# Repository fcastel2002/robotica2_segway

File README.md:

# Segway con patas extensibles

Trabajo final de **Robótica II**, Universidad Nacional de Cuyo (UNCUYO). Grupo 4: Joaquín Calderón
(modelado), Francisco Castel (diseño mecánico), Matías Armani (simulación en Simulink y electrónica), Ignacio Bartolini y Mariano Gimenez.

**Este archivo describe el robot tal como es hoy.** Todo lo que había de propuestas anteriores
(mecanismo de Hoeken, motores N20, plantas de simulación de agosto y principios de septiembre) se
borró del árbol el 19/9/2026 y quedó solo en la historia de git; ver la sección 7.

## Componentes comprados — actualización del 15/10/2026

El [inventario confirmado](electronica/componentes_comprados/inventario/inventario_robotica.md)
y los [datasheets y fichas recopilados](electronica/componentes_comprados/datasheets/README.md)
están organizados en [electrónica](electronica/componentes_comprados/README.md).
Se registran **14 entradas y 27 dispositivos/conjuntos** (un pack contiene tres celdas), incluidos **2 servos DSSERVO DS3240 MG** y
**2 motores GA25-370 de 12 V y 300 RPM con encoder**. ESP32 y MPU6050 confirmadas;
alimentación representada por una fuente nominal de 11,1 V. Matías es responsable de electrónica y PCB.
[Plan de trabajo](electronica/planificacion/2026-10-15-plan-electronica-pcb.md).

El modelo y la simulación **ya usan el motor comprado** desde el 15/10 (PAR-004 y ELE-014 en el
[backlog](BACKLOG.md)). Lo que sigue pendiente es el CAD, que todavía tiene el motor anterior de 37 mm
y al que le falta la rueda (CAD-202 y PAR-003). Cuidado con la ficha del vendedor: su columna de
torsión se contradice con la eléctrica, así que el par del modelo está **calculado**, no leído.

## 1. Qué es el robot

Un robot de dos ruedas que se equilibra como un péndulo invertido (tipo Segway) y que además tiene
**patas extensibles**: cada rueda cuelga de un mecanismo de cuatro barras movido por un servo, así
que el robot puede agacharse, pararse y bajar escalones absorbiendo el golpe con las patas.

- **Equilibrio y avance**: los dos motores de rueda, con encoder, controlados por un LQR sobre la
  inclinación y la velocidad (a diseñar sobre el modelo de la planta completa).
- **Patas**: un servo por pata. El servo es de posición; se le manda una trayectoria de ángulo y su
  lazo interno hace el par. La dinámica de la pata sirve para dimensionarlo, no para comandarlo.
- **Cabina**: caja impresa en PLA que lleva los dos servos, la batería y la electrónica. Los pivotes
  del cuatro barras (A, el eje del servo, y B) están en sus paredes laterales.

## 2. Números vigentes (19/9/2026)

Fuente única de todos los valores: [`modelado/parametros/parametros_fisicos.m`](modelado/parametros/parametros_fisicos.m),
variante `segunda_iteracion`. Si un número de este README no coincide con ese archivo, manda el archivo.

| | Valor | De dónde sale |
|---|---|---|
| Mecanismo | cuatro barras `A B C D` con acoplador rígido `C D P`; `P` es el eje de la rueda | `modelado/geometria/geometria_robot.png` |
| Barras | AD = 112, BC = 108, CD = 40,8, DP = 112 mm (familia 1,40 / 1,35 / 0,51 / 1,40 a escala 80); δ = 164° | medido en los STEP de `diseño_mecanico/segunda_iteracion/completo/step/` |
| Bancada AB | 80 mm a 45° (intención). En el STEP está en 77,9 mm a 46,6°: B quedó 3 mm corto en horizontal, a corregir en `cabeza_v31` | idem |
| Recorrido del servo | 320° (pata estirada, de pie) a 350° (plegada). En la dinámica se usa θ = 360° − servo: 10° plegada, 40° estirada | `parametros_geometria.m` |
| Rueda | Ø80 mm (Rw = 40), **50 g medidos** (22/10/2026) | Matías (radio), pesada |
| Servo de pata | **40 kg·cm**, ~58 g, uno por pata. Elegido el 19/9; verificar a qué tensión da los 40 kg·cm | decisión, ver sección 3 |
| Motor de rueda | **GA25-370 12 V, reductor 1:20, 300 rpm en vacío**, con encoder de cuadratura (11 PPR en el rotor). **96 g medidos** (22/10/2026). **Comprado** | decisión, ver sección 3 |
| Masas **medidas** (21 y 22/10/2026) | barras por pata: AD 30 g, BC 23 g, CDP 11 g (pesadas una por una); caja 542 g (se pesó el robot sin ruedas ni motores de rueda: 670 g, y se restaron las seis barras); rueda 50 g y motor de rueda 96 g; **robot 962 g** | el BC resultó **4 veces** más pesado que el estimado, la caja 19 % más liviana y la rueda 67 % más pesada. **Ya no queda ninguna masa estimada** |
| Batería | LiPo 3S 11,1 V (propuesta) | |
| Control | 200 Hz (propuesta); electrónica por definir | |

Lo que sale de esos números (par estático del servo, inercia vista por el servo, altura de la cabina,
qué escalón se puede bajar, fuerzas en los pasadores) está en los PDF de `modelado/`, sección 4.

## 3. Decisiones tomadas y por qué

| Fecha | Decisión | Motivo | Dónde está |
|---|---|---|---|
| ago 2026 | Mecanismo de Hoeken con flexor → **cuatro barras** con acoplador rígido | el cuatro barras da una línea casi recta para el eje de rueda con un solo servo, y es más fácil de imprimir | `modelado/geometria/` |
| 2/9 | Barras en la familia 1,40 / 1,35 / 0,51 / 1,40 con δ = 164° | salió de un barrido de proporciones (scripts de Francisco, ya borrados; ver sección 7) | `parametros_fisicos.m` |
| 3/9 | Motor JGA25 de 60 rpm **descartado** | la simulación mostró que con 60 rpm el robot equilibra pero no puede desplazarse ni bajar escalones; hace falta encoder sí o sí | `base_conocimiento/dimensiones_cad_primera_iteracion.md` |
| 14/9 | CAD segunda iteración: barras a **escala 80** | la primera iteración tenía la bancada de 80 mm con barras de escala 100 y perdía la línea recta; Francisco llevó las barras a 80 | `diseño_mecanico/segunda_iteracion/` |
| 19/9 | El modelado pasa a escala 80 para seguir al CAD | eran dos ramas de la misma bifurcación; imprimir es lo caro, así que manda el CAD | `docs/gestion/2026-09-19-auditoria-limpieza.md`, sección 1.2 |
| 19/9 | Servo de **40 kg·cm** | con la geometría de escala 100 la caída de un escalón de 18 cm pedía 22,4 kg·cm de par medio; uno de 25 quedaba justo y uno de 35 no se consigue | `modelado/dinamica/dinamica_resumen.pdf`, sección 10 |
| 15/10 | Motor de rueda **GA25-370 1:20** (comprado) | 300 rpm en vacío dan 1,01 m/s con la rueda de 66 mm. El par y el agarre quedan casi empatados: el motor pone 6,0 N en el piso contra 6,9 N de fricción disponible. La columna de torsión de su ficha es inconsistente y no se usa | `modelado/parametros/parametros_fisicos.m` §7 |
| 19/9 | `simulacion/planta_v2` (planta completa hecha con Claude) se descarta | el equipo va a rehacer la planta a mano en `modelado/planta/`; queda el banco Simulink de Matías | sección 7 |

## 4. Mapa del repositorio

Nuevo el 1/10/2026: [**modelo dinámico del péndulo invertido, desarrollado paso a paso**](modelado/planta/pendulo_invertido/desarrollo_matematico.md).
Representa el equilibrio y avance con las patas fijas en una postura configurable. La demostración
en MATLAB está en [`simulacion/pendulo_invertido/`](simulacion/pendulo_invertido/README.md); abrir
`SIMULAR_PENDULO_INVERTIDO.m` y pulsar Run. La planta conjunta con flexión dinámica sigue pendiente.

| Carpeta | Qué hay | Responsable |
|---|---|---|
| [`modelado/`](modelado/) | **El modelo del robot.** Una carpeta por tema: `geometria/` (figura con nombres y cotas), `cinematica/` (θ → posiciones, directa e inversa), `dcl/` (diagramas de cuerpo libre), `dinamica/` (Lagrange de la pata, tres casos, caída de escalón, fuerza en el eje del servo), `parametros/` (la fuente única de valores). Cada tema tiene su PDF con la deducción. Ver [`modelado/README.md`](modelado/README.md) | Joaquín (modelado), Matías (API y `parametros/`) |
| [`diseño_mecanico/`](diseño_mecanico/) | `3er_iteracion/`: el CAD vigente de la pata (SolidWorks + STEP). `chasis nuevo/`: ensamble del chasis con la cabina, el servo y el lugar de la PCB. `utilidades/`: piezas compradas (servo, horn, motores, sensor, rueda, tornillería). Las iteraciones anteriores se borraron el 1/11 y siguen en git. Ver [`diseño_mecanico/README.md`](diseño_mecanico/README.md) | Francisco |
| [`simulacion/`](simulacion/) | `dinamica_pata_v1/`: primera iteración del banco Simulink de la pata (Matías, 14 y 15/9), punto de entrada `INICIAR_DINAMICA_PATA.m`. Ver [`simulacion/README.md`](simulacion/README.md) | Matías |
| [`ensayos/`](ensayos/README.md) | Experimentos con el robot real, repetibles: un protocolo `.json` por experimento, `correr.py` lo ejecuta por WiFi y deja una carpeta por corrida, `revisar.py` controla lo grabado. Nació con la cosimulación robot ↔ Simulink (9/11) | Francisco |
| [`gui_hmi/`](gui_hmi/) | Interfaz web para ver las variables del robot en tiempo real (WiFi o USB) y grabarlas a CSV. `python gui_hmi/puente.py --simular` y abrir http://localhost:8000. Ver [`gui_hmi/README.md`](gui_hmi/README.md) | |
| [`docs/gestion/`](docs/gestion/) | Plan, guía de QA y traspaso del banco Simulink; auditoría de limpieza del 19/9 | Matías, Joaquín |
| [`base_conocimiento/`](base_conocimiento/) | `dimensiones_cad_primera_iteracion.md`: cotas, masas, centros de masa e inercias medidos sobre el STEP de la primera iteración (2/9). Sigue vigente para masas; para cotas manda la segunda iteración | |
| [`guias_catedra/`](guias_catedra/) | Procedimientos de la cátedra (dimensionamiento de batería, preselección de servos) | |
| [`BACKLOG.md`](BACKLOG.md) | Lo hecho, lo en curso y lo pendiente, con evidencia. Es la lista de tareas del equipo | todos |
| [`AGENTS.md`](AGENTS.md) | Reglas para agentes y colaboradores (PDF → Markdown antes de leer, backlog, diagramas) | |
| [`electronica/`](electronica/README.md) | Inventario de compras, capturas, datasheets, fichas y fuentes; integración eléctrica pendiente | Matías |
| `firmware/`, `referencias/` | Firmware pendiente; referencias de apoyo | |

## 5. Qué falta (lo grande)

Detalle y estado en [`BACKLOG.md`](BACKLOG.md).

1. ~~**Pesar** las piezas impresas, el servo y el motor~~: hecho el 21 y el 22/10/2026 (robot de 962 g). Falta la inercia de la rueda (disco o aro), ver M-4 del [plan de ensayos](docs/gestion/2026-10-21-plan-de-ensayos.md).
2. **Medir el motor**: par de bloqueo real con un brazo y una balanza, y rendimiento del reductor. La ficha del GA25-370 se contradice a sí misma (su columna de torsión exigiría 146 % de rendimiento), así que el par del modelo está calculado, no leído.
3. **Medir el servo** en el banco: rigidez del lazo interno (grados de desvío por peso colgado) y par de
   calado real a la tensión que se use. De eso dependen todos los números de la caída de escalón.
4. Corregir en el CAD los 3 mm de la bancada (`cabeza_v31`) y agregar rueda, motor y tapa al ensamble
   de la segunda iteración, para poder cerrar la ficha de masas (CAD-201).
5. **Planta completa** en `modelado/planta/`: péndulo invertido sobre ruedas con la altura del centro de
   masa en función de θ, LQR, motores, contacto. Es el modelo del equilibrio; el banco de Matías es el
   de la pata.
6. Electrónica: [plan, requisitos y ensayos definidos](electronica/README.md); validar el prototipo y después diseñar la PCB. Firmware de prueba e integración pendientes.

## 6. Cómo correr las cosas

- Figuras: `python modelado/<tema>/<figura>.py` genera el PNG al lado (Python 3 + matplotlib).
- Dinámica de la pata: abrir `modelado/dinamica/dinamica_pata.m` en MATLAB y correrlo. La sección 1
  tiene los parámetros para editar; las demás imprimen tablas y grafican.
- Tests: desde la raíz, `runtests('modelado/dinamica/tests')` y
  `runtests('simulacion/dinamica_pata_v1/tests')`.
- Banco Simulink: `simulacion/dinamica_pata_v1/INICIAR_DINAMICA_PATA.m` (ver su README).
- PDF: cada `*.tex` se compila con `pdflatex` dos veces desde su carpeta.
- Medir el CAD sin SolidWorks: los scripts de `diseño_mecanico/medir_step/` se borraron el 1/11; se recuperan con
  `git checkout 2867761 -- "diseño_mecanico/medir_step"`.

## 7. Historia: lo que hubo antes y dónde encontrarlo

Hasta el 19/9 el repo arrastraba tres diseños anteriores y sus simulaciones, y cualquiera que entrara
(persona o IA) no sabía cuál era el vigente. Se borró todo lo anterior al cuatro barras y las plantas
de simulación descartadas. La lista completa, con el motivo de cada borrado, está en
[`docs/gestion/2026-09-19-auditoria-limpieza.md`](docs/gestion/2026-09-19-auditoria-limpieza.md).
Todo sigue en git: `git show eca3ed4:<ruta>` recupera cualquier archivo tal como estaba antes de la limpieza.

| Qué era | Dónde estaba | Por qué ya no |
|---|---|---|
| Mecanismo de Hoeken, robot de 800 g con rueda Ø80 y flexor (documento de dimensionamiento de agosto) | `base_conocimiento/Segway-Pata-Dimensionamiento.docx`, `simulacion/hoekens_dh.html` | reemplazado por el cuatro barras |
| Concepto con motores N20 y microservos SG90 | `diseño_mecanico/proof_of_concept/` | reemplazado |
| Primer boceto del cuatro barras y síntesis en MotionGen | `diseño_mecanico/4_bar_mechanism/`, `4 barras.motiongen` | reemplazado por `primera_iteracion` |
| GUI y barrido de proporciones de las barras (Francisco, 28/8) | `simulacion/simular_pata_segway.m`, `optimizar_barrido_local.m` | cumplieron su función; las proporciones quedaron en `parametros_fisicos.m` |
| CAD primera iteración (bancada 80 a 47,5°, barras 100) | `diseño_mecanico/primera_iteracion/*.SLDPRT` | reemplazado por la segunda; queda el STEP y las masas |
| CAD primera y segunda iteración, soporte de mesa, STEP para imprimir y scripts `medir_step` (borrados el 1/11/2026) | `diseño_mecanico/primera_iteracion/`, `segunda_iteracion/`, `soporte_mesa/`, `step_printing/`, `medir_step/`, `outputs/` | Francisco dejó solo `3er_iteracion/`, `chasis nuevo/` y `utilidades/`; se recuperan con `git checkout 2867761 -- "diseño_mecanico/<carpeta>"` |
| Plantas Simulink `modelo_base`, `planta_v1` (borradas el 13/9) y `planta_v2` (19/9), con su manual y sus specs | `simulacion/`, `docs/informe_planta_v1/`, `docs/superpowers/` | el equipo rehace la planta a mano; queda el banco de Matías |
| Toolbox de Peter Corke copiado entero (120 MB) | `modelado/cinematica/rtb`, `smtb`, `common` | librería de terceros; `verificar_cinematica_4barras.m` sigue andando sin ella |

## 8. Convenciones

- Origen en A (eje del servo), y hacia arriba. En las figuras de la pata el frente del robot queda a la
  izquierda. Los segmentos se nombran por sus extremos: AB, AD, BC, CD, DP.
- Los PDF no se leen directamente: se convierten a Markdown primero (regla de [`AGENTS.md`](AGENTS.md)).
- Un valor físico vive en un solo lugar, `parametros_fisicos.m`. Las figuras de Python repiten las
  cinco cotas al principio de cada script porque no leen MATLAB; si cambian las barras, cambiarlas ahí también.

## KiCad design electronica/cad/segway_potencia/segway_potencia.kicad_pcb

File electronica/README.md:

# Electrónica

**Para continuar en una sesión nueva de Claude Code: [INICIAR_AQUI.md](INICIAR_AQUI.md).** Abrir Claude Code desde la raíz del repositorio. Camino confirmado: **KiCad + IA + MCP**, en **Windows**; Matías instalará KiCad. Estado al día en [estado actual](agente/memoria/estado_actual.md).

- [Plan de electrónica y PCB](planificacion/2026-10-15-plan-electronica-pcb.md).
- Borradores del 17/10: [contrato de interfaces](interfaces/2026-10-17-contrato-interfaces-borrador.md), [distribución de energía](interfaces/2026-10-17-distribucion-energia-borrador.md), [datos físicos faltantes](componentes_comprados/2026-10-17-datos-fisicos-faltantes.md).
- Entorno: [informe Windows](agente/2026-10-17-informe-entorno-windows.md) y [evaluación de MCP para KiCad](agente/2026-10-17-evaluacion-mcp-kicad.md).
- [Research de Reddit sobre EDA con IA y MCP](planificacion/2026-10-15-research-reddit-eda-ia.md).
- [Requisitos y decisiones](requisitos_y_decisiones.md).
- [Ensayos de banco](ensayos/plan_de_ensayos.md).
- [Componentes comprados y documentación](componentes_comprados/README.md).
- [Inventario detallado](componentes_comprados/inventario/inventario_robotica.md).
- [Datasheets, fichas y fuentes](componentes_comprados/datasheets/README.md).

Actualizado el 15 de octubre de 2026. Las compras confirmadas incluyen dos DS3240 MG y dos GA25-370 de 12 V y 300 RPM con encoder. La validación eléctrica de los módulos genéricos y la integración con CAD/modelado siguen pendientes en [BACKLOG.md](../BACKLOG.md).

Controladora e IMU confirmadas: **ESP32 y MPU6050**. Alimentación representada como **fuente nominal de 11,1 V** por pedido de Matías. Responsable de electrónica y PCB: **Matías**.

**Criterio confirmado para las PCB (15/10/2026):** usar los componentes como módulos completos con pines o sus conexiones físicas reales. La placa interconecta estos módulos. Aplicar [REQ-22 y sus criterios de símbolos, huellas y montaje](requisitos_y_decisiones.md) en todo diseño.

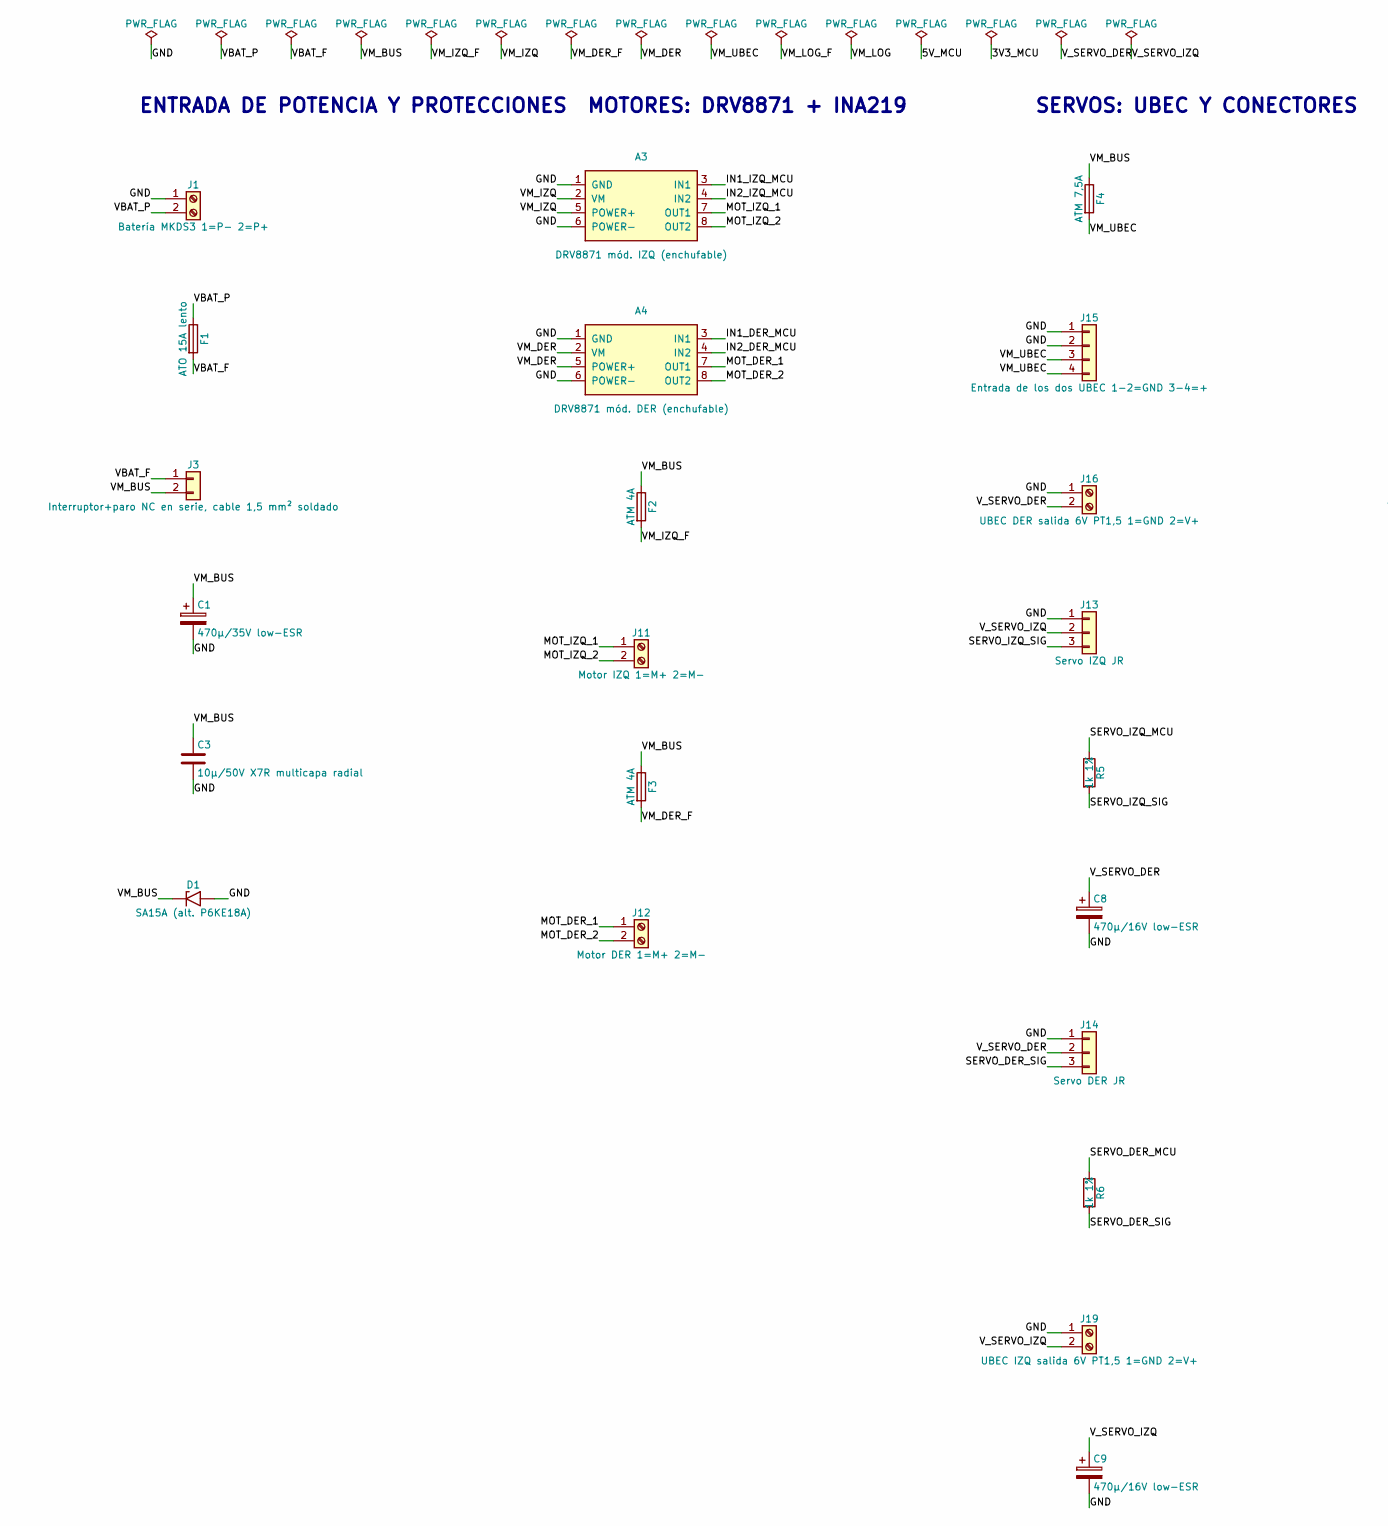
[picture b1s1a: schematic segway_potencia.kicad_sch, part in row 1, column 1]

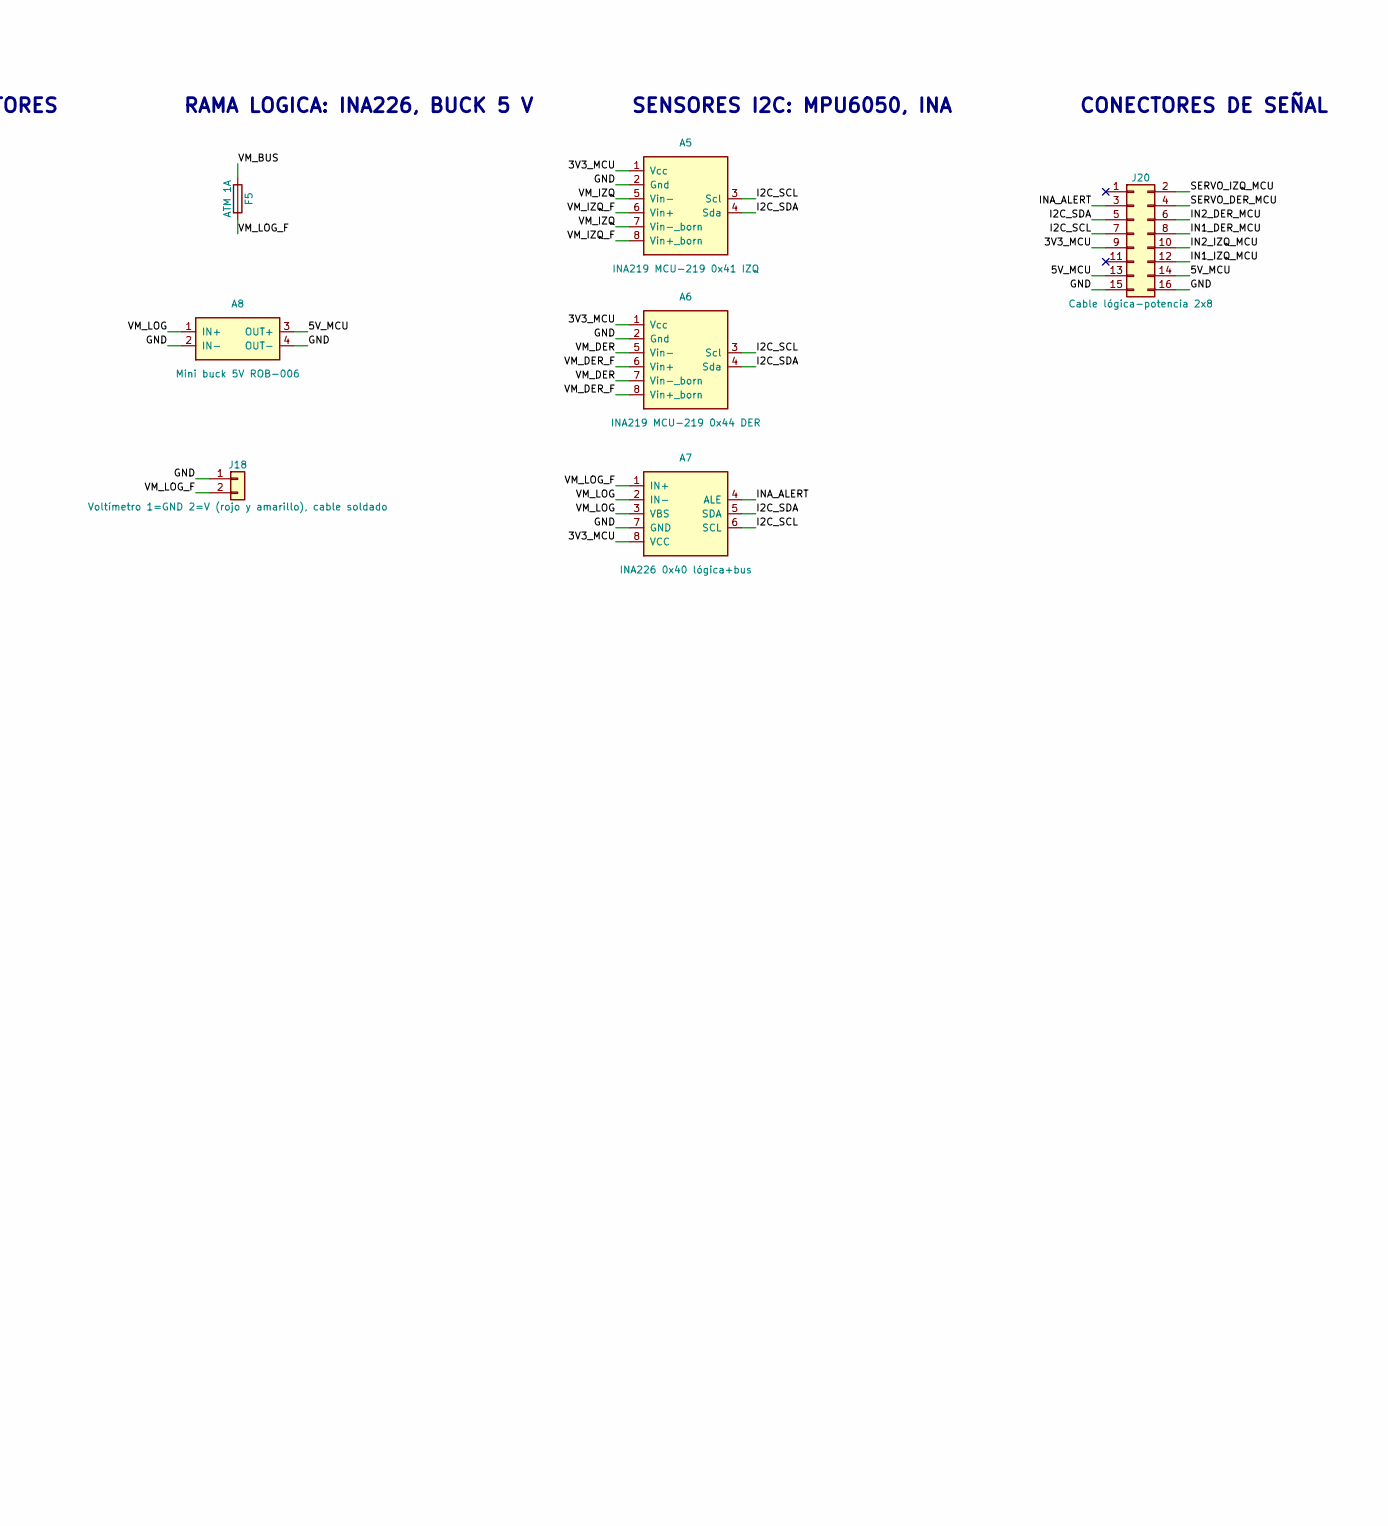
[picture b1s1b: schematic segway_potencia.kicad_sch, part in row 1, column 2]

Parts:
A3: DRV8871 mód. IZQ (enchufable); ROB-008_DRV8871_modulo_8p
A4: DRV8871 mód. DER (enchufable); ROB-008_DRV8871_modulo_8p
A5: INA219 MCU-219 0x41 IZQ; ROB-002_INA219_MCU-219_8p
A6: INA219 MCU-219 0x44 DER; ROB-002_INA219_MCU-219_8p
A7: INA226 0x40 lógica+bus; ROB-009_INA226_modulo_8p
A8: Mini buck 5V ROB-006; ROB-005-006_MiniBuck_modulo_4p
C1: 470µ/35V low-ESR; CP_Radial_D10.0mm_P5.00mm
C3: 10µ/50V X7R multicapa radial; C_Disc_D7.5mm_W5.0mm_P5.00mm
C8, C9: 470µ/16V low-ESR; CP_Radial_D8.0mm_P3.50mm
D1: SA15A (alt. P6KE18A); D_DO-15_P10.16mm_Horizontal
F1: ATO 15A lento; Fuseholder_Blade_ATO_Littelfuse_Pudenz_2_Pin
F2, F3: ATM 4A; Fuseholder_Blade_Mini_Keystone_3568
F4: ATM 7,5A; Fuseholder_Blade_Mini_Keystone_3568
F5: ATM 1A; Fuseholder_Blade_Mini_Keystone_3568
J1: Batería MKDS3 1=P− 2=P+; TerminalBlock_Phoenix_MKDS-3-2-5.08_1x02_P5.08mm_Horizontal
J3: Interruptor+paro NC en serie, cable 1,5 mm² solda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; SolderWire-1.5sqmm_1x02_P6mm_D1.7mm_OD3mm
J11: Motor IZQ 1=M+ 2=M−; TerminalBlock_Phoenix_MKDS-1,5-2-5.08_1x02_P5.08mm_Horizont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
J12: Motor DER 1=M+ 2=M−; TerminalBlock_Phoenix_MKDS-1,5-2-5.08_1x02_P5.08mm_Horizont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
J13: Servo IZQ JR; PinHeader_1x03_P2.54mm_Vertical
J14: Servo DER JR; PinHeader_1x03_P2.54mm_Vertical
J15: Entrada de los dos UBEC 1-2=GND 3-4=+; TerminalBlock_Phoenix_MKDS-1,5-4-5.08_1x04_P5.08mm_Horizont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
J16: UBEC DER salida 6V PT1,5 1=GND 2=V+; TerminalBlock_Phoenix_PT-1,5-2-3.5-H_1x02_P3.50mm_Horizontal
J18: Voltímetro 1=GND 2=V (rojo y amarillo), cable sol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; SolderWire-0.5sqmm_1x02_P4.6mm_D0.9mm_OD2.1mm
J19: UBEC IZQ salida 6V PT1,5 1=GND 2=V+; TerminalBlock_Phoenix_PT-1,5-2-3.5-H_1x02_P3.50mm_Horizontal
J20: Cable lógica-potencia 2x8; IDC-Header_2x08_P2.54mm_Vertical
R5, R6: 1k 1%; R_Axial_DIN0207_L6.3mm_D2.5mm_P10.16mm_Horizontal

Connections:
/3V3_MCU: A5.1 (Vcc), A6.1 (Vcc), A7.8 (VCC), J20.9
/5V_MCU: A8.3 (OUT+), J20.13, J20.14; also elsewhere on the board
/GND: A3.1 (GND), A3.6 (POWER-), A4.1 (GND), A4.6 (POWER-), A5.2 (Gnd), A6.2 (Gnd), A7.7 (GND), A8.2 (IN-), A8.4 (OUT-), C1.2, C3.2, C8.2, C9.2, D1.2 (A2), J1.1, J13.1, J14.1, J15.1, J15.2, J16.1, J18.1, J19.1, J20.15, J20.16; also elsewhere on the board
/I2C_SCL: A5.3 (Scl), A6.3 (Scl), A7.6 (SCL), J20.7
/I2C_SDA: A5.4 (Sda), A6.4 (Sda), A7.5 (SDA), J20.5
/IN1_DER_MCU: A4.3 (IN1), J20.8
/IN1_IZQ_MCU: A3.3 (IN1), J20.12
/IN2_DER_MCU: A4.4 (IN2), J20.6
/IN2_IZQ_MCU: A3.4 (IN2), J20.10
/INA_ALERT: A7.4 (ALE), J20.3
/MOT_DER_1: A4.7 (OUT1), J12.1
/MOT_DER_2: A4.8 (OUT2), J12.2
/MOT_IZQ_1: A3.7 (OUT1), J11.1
/MOT_IZQ_2: A3.8 (OUT2), J11.2
/SERVO_DER_MCU: J20.4, R6.1
/SERVO_DER_SIG: J14.3, R6.2
/SERVO_IZQ_MCU: J20.2, R5.1
/SERVO_IZQ_SIG: J13.3, R5.2
/VBAT_F: F1.2, J3.1
/VBAT_P: F1.1, J1.2
/VM_BUS: C1.1, C3.1, D1.1 (A1), F2.1, F3.1, F4.1, F5.1, J3.2
/VM_DER: A4.2 (VM), A4.5 (POWER+), A6.5 (Vin-), A6.7 (Vin-_born)
/VM_DER_F: A6.6 (Vin+), A6.8 (Vin+_born), F3.2
/VM_IZQ: A3.2 (VM), A3.5 (POWER+), A5.5 (Vin-), A5.7 (Vin-_born)
/VM_IZQ_F: A5.6 (Vin+), A5.8 (Vin+_born), F2.2
/VM_LOG: A7.2 (IN-), A7.3 (VBS), A8.1 (IN+)
/VM_LOG_F: A7.1 (IN+), F5.2, J18.2
/VM_UBEC: F4.2, J15.3, J15.4
/V_SERVO_DER: C8.1, J14.2, J16.2
/V_SERVO_IZQ: C9.1, J13.2, J19.2

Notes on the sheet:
MOTORES: DRV8871 + INA219
SENSORES I2C: MPU6050, INA
ENTRADA DE POTENCIA Y PROTECCIONES
SERVOS: UBEC Y CONECTORES
RAMA LOGICA: INA226, BUCK 5 V
CONECTORES DE SEÑAL

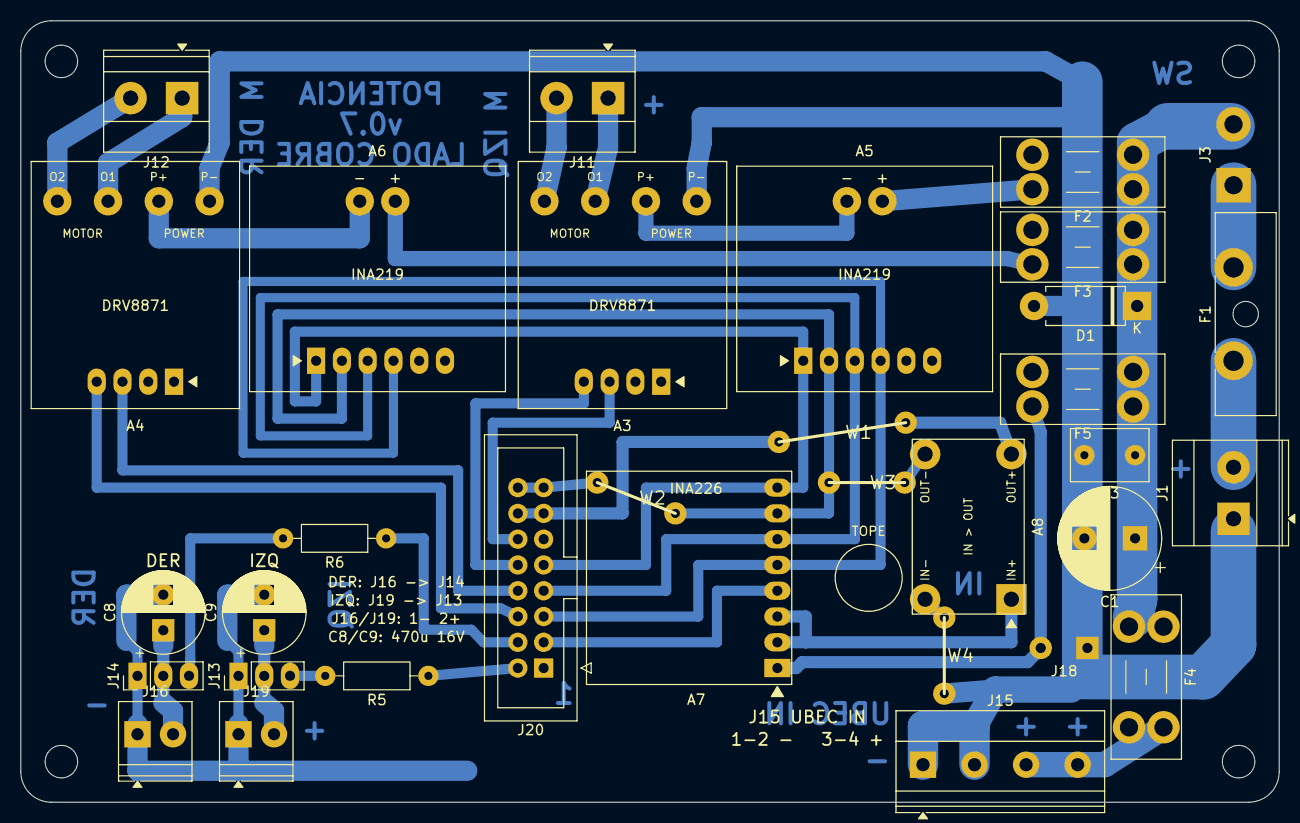
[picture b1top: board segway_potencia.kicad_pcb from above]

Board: 2 copper layers, 124.0 x 77.0 mm, 37 parts (0 on the bottom side), 30 nets.

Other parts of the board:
H1, H2, H3, H4: M3; MountingHole_3.2mm_M3
W1: puente 12.6 mm; Puente_alambre
W2: puente 8.3 mm; Puente_alambre
W3, W4: puente 7.5 mm; Puente_alambre

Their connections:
/5V_MCU: W1.1; also elsewhere on the board
/GND: W2.1, W3.1, W4.1; also elsewhere on the board

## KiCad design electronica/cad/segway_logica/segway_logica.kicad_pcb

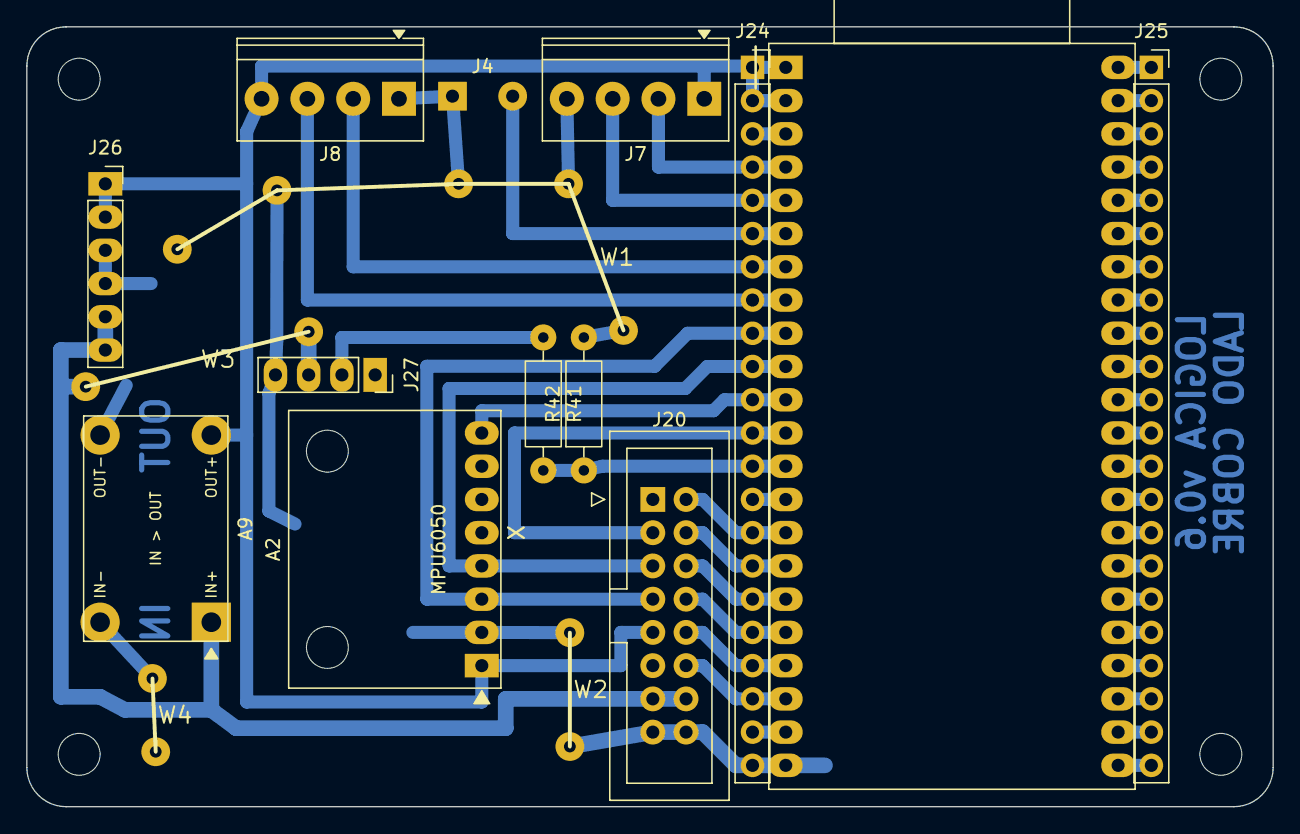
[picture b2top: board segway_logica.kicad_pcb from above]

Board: 2 copper layers, 95.2 x 59.6 mm, 21 parts (0 on the bottom side), 42 nets.

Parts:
A1: ESP32-S3-DevKitC-1 N16R8; ROB-012_ESP32-S3-DevKitC-1_N16R8_44p
A2: GY-521 MPU6050 0x68; ROB-013_MPU6050_modulo_8p
A9: Mini buck 3,3V ROB-005; ROB-005-006_MiniBuck_modulo_4p
H1, H2, H3, H4: M3; MountingHole_3.2mm_M3
J4: Paro NC 1=GND 2=PARO, cable soldado; SolderWire-0.5sqmm_1x02_P4.6mm_D0.9mm_OD2.1mm
J7: Encoder IZQ PT1,5 1=V 2=A 3=B 4=GND; TerminalBlock_Phoenix_PT-1,5-4-3.5-H_1x04_P3.50mm_Horizontal
J8: Encoder DER PT1,5 1=GND 2=A 3=B 4=V; TerminalBlock_Phoenix_PT-1,5-4-3.5-H_1x04_P3.50mm_Horizontal
J20: Cable lógica-potencia 2x8; IDC-Header_2x08_P2.54mm_Vertical
J24: Expansión ESP32 IZQ (A1.1-22); Zocalo_expansion_izq_1x22_P2.54mm
J25: Expansión ESP32 DER (A1.23-44); Zocalo_expansion_der_1x22_P2.54mm
J26: Alim. sensores 1-2 3V3 3-4 GND 5-6 5V; PinSocket_1x06_P2.54mm_Vertical
J27: Sharp GP2Y0A60SZLF (Pololu 2474) 1=EN 2=OUT 3=VCC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; PinSocket_1x04_P2.54mm_Vertical
R41: 10k 1%; R_Axial_DIN0207_L6.3mm_D2.5mm_P10.16mm_Horizontal
R42: 15k 1%; R_Axial_DIN0207_L6.3mm_D2.5mm_P10.16mm_Horizontal
W1: puente 43.1 mm; Puente_alambre
W2: puente 8.7 mm; Puente_alambre
W3: puente 17.5 mm; Puente_alambre
W4: puente 5.6 mm; Puente_alambre

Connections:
/3V3_MCU: A1.1, A1.2, A2.1, A9.3, J7.1, J8.4, J20.9, J24.1, J24.2, J26.1, J26.2
/5V_MCU: A9.1, J20.13, J20.14, J26.5, J26.6, J27.3, W3.1
/5V_USB: A1.21, J24.21
/DIST_SUELO: A1.13, J24.13, R41.2, R42.1
/ENC_DER_A: A1.7, J8.2, J24.7
/ENC_DER_B: A1.8, J8.3, J24.8
/ENC_IZQ_A: A1.4, J7.2, J24.4
/ENC_IZQ_B: A1.5, J7.3, J24.5
/GND: A1.22, A1.23, A1.43, A1.44, A2.2, A9.2, A9.4, J4.1, J7.4, J8.1, J20.15, J20.16, J24.22, J25.1, J25.21, J25.22, J26.3, J26.4, J27.4, R42.2, W1.1, W2.1, W4.1
/GPIO0: A1.36, J25.14
/GPIO1: A1.26, J25.4
/GPIO2: A1.27, J25.5
/GPIO19: A1.42, J25.20
/GPIO20: A1.41, J25.19
/GPIO21: A1.40, J25.18
/GPIO35: A1.35, J25.13
/GPIO36: A1.34, J25.12
/GPIO37: A1.33, J25.11
/GPIO38: A1.32, J25.10
/GPIO39: A1.31, J25.9
/GPIO40: A1.30, J25.8
/GPIO41: A1.29, J25.7
/GPIO42: A1.28, J25.6
/GPIO43: A1.24, J25.2
/GPIO44: A1.25, J25.3
/GPIO45: A1.37, J25.15
/GPIO46: A1.14, J24.14
/GPIO47: A1.39, J25.17
/GPIO48: A1.38, J25.16
/I2C_SCL: A1.9, A2.3, J20.7, J24.9
/I2C_SDA: A1.10, A2.4, J20.5, J24.10
/IMU_INT: A1.11, A2.8, J24.11
/IN1_DER_MCU: A1.18, J20.8, J24.18
/IN1_IZQ_MCU: A1.20, J20.12, J24.20
/IN2_DER_MCU: A1.17, J20.6, J24.17
/IN2_IZQ_MCU: A1.19, J20.10, J24.19
/INA_ALERT: A1.12, J20.3, J24.12
/PARO_CONT: A1.6, J4.2, J24.6
/RST: A1.3, J24.3
/SERVO_DER_MCU: A1.16, J20.4, J24.16
/SERVO_IZQ_MCU: A1.15, J20.2, J24.15
/SHARP_OUT: J27.2, R41.1

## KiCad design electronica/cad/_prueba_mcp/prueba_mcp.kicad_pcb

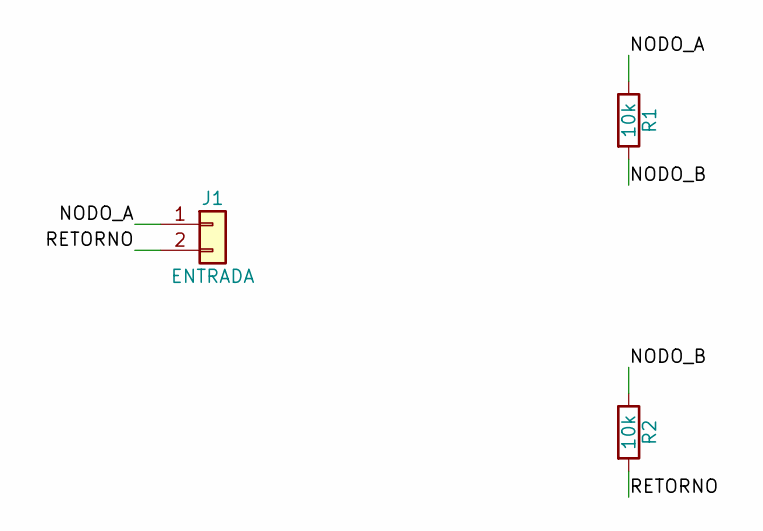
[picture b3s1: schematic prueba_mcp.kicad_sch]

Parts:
J1: ENTRADA; PinHeader_1x02_P2.54mm_Vertical
R1, R2: 10k; R_Axial_DIN0207_L6.3mm_D2.5mm_P7.62mm_Horizontal

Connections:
/NODO_A: J1.1, R1.1
/NODO_B: R1.2, R2.1
/RETORNO: J1.2, R2.2

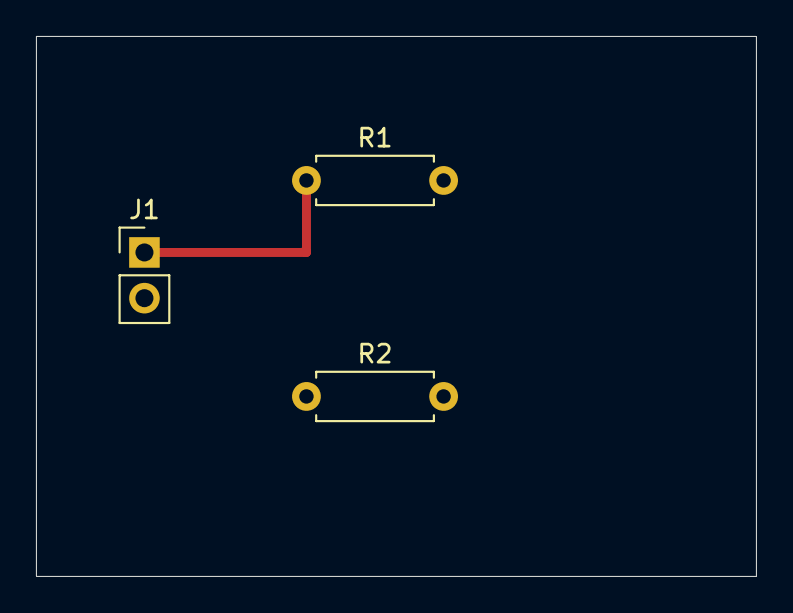
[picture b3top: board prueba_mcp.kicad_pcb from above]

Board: 2 copper layers, 40.0 x 30.0 mm, 3 parts (0 on the bottom side), 3 nets.
